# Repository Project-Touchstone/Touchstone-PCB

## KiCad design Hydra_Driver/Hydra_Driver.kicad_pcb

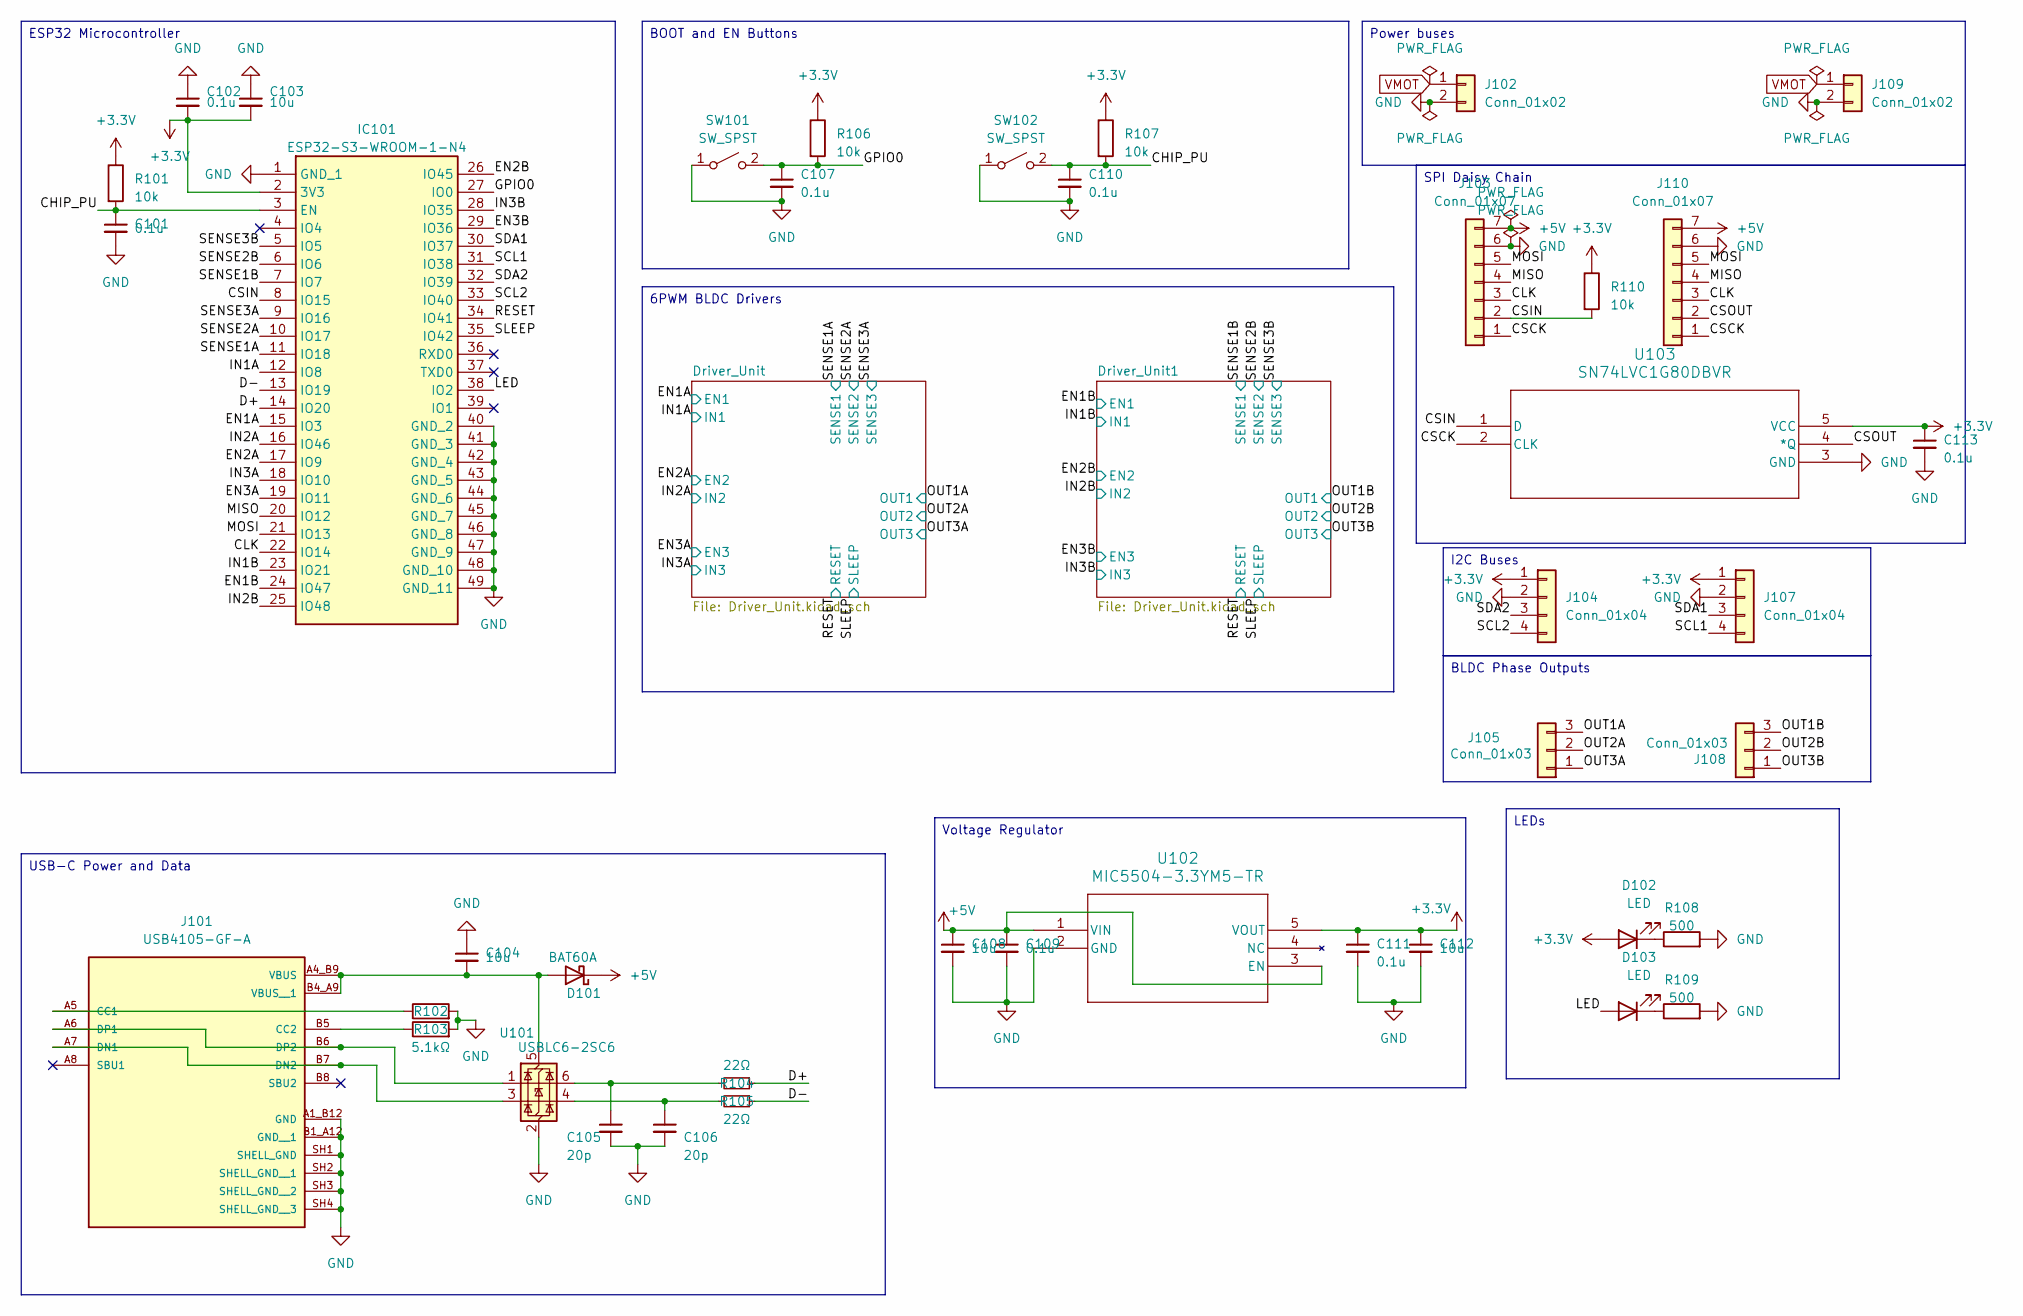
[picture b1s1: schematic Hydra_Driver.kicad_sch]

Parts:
C101, C102, C107, C109, C110, C111, C113: 0.1u; C_0402_1005Metric
C103, C104, C108, C112: 10u; C_0805_2012Metric
C105, C106: 20p; C_0402_1005Metric; LCSC C1648
D101: BAT60A; D_SOD-323; JLCPCB C124187
D102, D103: LED; LED_0603_1608Metric
IC101: ESP32-S3-WROOM-1-N4; ESP32S3WROOM1N4; Manufacturer_Part_Number ESP32-S3-WROOM-1-N4; Mouser Part Number 356-ESP32-S3WROOM1N4
J101: USB4105-GF-A; GCT_USB4105-GF-A; PARTREV B4
J102, J109: Conn_01x02; AMASS_XT30U-F_1x02_P5.0mm_Vertical
J103: Conn_01x07; PinSocket_1x07_P2.54mm_Horizontal
J104, J107: Conn_01x04; CONN_CCSH-W10R-04TR-BK-A_ADA
J105, J108: Conn_01x03; JST_XH_S3B-XH-A-1_1x03_P2.50mm_Horizontal
J110: Conn_01x07; PinHeader_1x07_P2.54mm_Horizontal
R101, R106, R107, R110: 10k; R_0402_1005Metric
R102, R103: 5.1kΩ; R_0402_1005Metric; JLCPCB C23186
R104, R105: 22Ω; R_0402_1005Metric; LCSC C23345
R108, R109: 500; R_0402_1005Metric
SW101, SW102: SW_SPST; SW_B3U-1000P
U101: USBLC6-2SC6; SOT-23-6; JLCPCB C2827654
U102: MIC5504-3.3YM5-TR; SOT-23-5_MC_MCH
U103: SN74LVC1G80DBVR; DBV5

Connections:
+3.3V: C102.2, C103.2, C111.1, C112.1, C113.1, D102.2 (A), IC101.2 (3V3), J104.1, J107.1, R101.1, R106.1, R107.1, R110.1, U102.5 (VOUT), U103.5 (VCC); also elsewhere on the board
+5V: C108.1, C109.1, D101.1 (K), J103.7, J110.7, U102.1 (VIN), U102.3 (EN)
/CHIP_PU: C101.1, C110.1, IC101.3 (EN), R101.2, R107.2, SW102.2 (B)
/CLK: IC101.22 (IO14), J103.3, J110.3
/CSCK: J103.1, J110.1, U103.2 (CLK)
/CSIN: IC101.8 (IO15), J103.2, R110.2, U103.1 (D)
/CSOUT: J110.2, U103.4 (*Q)
/D+: IC101.14 (IO20), R104.1
/D-: IC101.13 (IO19), R105.1
/EN1A: IC101.15 (IO3); also elsewhere on the board
/EN1B: IC101.24 (IO47); also elsewhere on the board
/EN2A: IC101.17 (IO9); also elsewhere on the board
/EN2B: IC101.26 (IO45); also elsewhere on the board
/EN3A: IC101.19 (IO11); also elsewhere on the board
/EN3B: IC101.29 (IO36); also elsewhere on the board
/GPIO0: C107.1, IC101.27 (IO0), R106.2, SW101.2 (B)
/IN1A: IC101.12 (IO8); also elsewhere on the board
/IN1B: IC101.23 (IO21); also elsewhere on the board
/IN2A: IC101.16 (IO46); also elsewhere on the board
/IN2B: IC101.25 (IO48); also elsewhere on the board
/IN3A: IC101.18 (IO10); also elsewhere on the board
/IN3B: IC101.28 (IO35); also elsewhere on the board
/LED: D103.2 (A), IC101.38 (IO2)
/MISO: IC101.20 (IO12), J103.4, J110.4
/MOSI: IC101.21 (IO13), J103.5, J110.5
/OUT1A: J105.3; also elsewhere on the board
/OUT1B: J108.3; also elsewhere on the board
/OUT2A: J105.2; also elsewhere on the board
/OUT2B: J108.2; also elsewhere on the board
/OUT3A: J105.1; also elsewhere on the board
/OUT3B: J108.1; also elsewhere on the board
/RESET: IC101.34 (IO41); also elsewhere on the board
/SCL1: IC101.31 (IO38), J107.4
/SCL2: IC101.33 (IO40), J104.4
/SDA1: IC101.30 (IO37), J107.3
/SDA2: IC101.32 (IO39), J104.3
/SENSE1A: IC101.11 (IO18); also elsewhere on the board
/SENSE1B: IC101.7 (IO7); also elsewhere on the board
/SENSE2A: IC101.10 (IO17); also elsewhere on the board
/SENSE2B: IC101.6 (IO6); also elsewhere on the board
/SENSE3A: IC101.9 (IO16); also elsewhere on the board
/SENSE3B: IC101.5 (IO5); also elsewhere on the board
/SLEEP: IC101.35 (IO42); also elsewhere on the board
GND: C101.2, C102.1, C103.1, C104.1, C105.2, C106.2, C107.2, C108.2, C109.2, C110.2, C111.2, C112.2, C113.2, IC101.1 (GND_1), IC101.40 (GND_2), IC101.41 (GND_3), IC101.42 (GND_4), IC101.43 (GND_5), IC101.44 (GND_6), IC101.45 (GND_7), IC101.46 (GND_8), IC101.47 (GND_9), IC101.48 (GND_10), IC101.49 (GND_11), J101.A1_B12 (GND), J101.B1_A12 (GND__1), J101.SH1 (SHELL_GND), J101.SH2 (SHELL_GND__1), J101.SH3 (SHELL_GND__2), J101.SH4 (SHELL_GND__3), J102.2, J103.6, J104.2, J107.2, J109.2, J110.6, R102.2, R103.2, R108.2, R109.2, SW101.1 (A), SW102.1 (A), U101.2 (GND), U102.2 (GND), U103.3 (GND); also elsewhere on the board
unnamed: C105.1, R104.2, U101.6 (I/O1)
unnamed: C106.1, R105.2, U101.4 (I/O2)
unnamed: C104.2, D101.2 (A), J101.A4_B9 (VBUS), J101.B4_A9 (VBUS__1), U101.5 (VBUS)
unnamed: D102.1 (K), R108.1
unnamed: D103.1 (K), R109.1
unnamed: J101.A5 (CC1), R102.1
unnamed: J101.B5 (CC2), R103.1
unnamed: J101.A7 (DN1), J101.B7 (DN2), U101.3 (I/O2)
unnamed: J101.A6 (DP1), J101.B6 (DP2), U101.1 (I/O1)
VMOT: J102.1, J109.1; also elsewhere on the board

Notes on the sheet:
BLDC Phase Outputs
I2C Buses
LEDs
ESP32 Microcontroller
BOOT and EN Buttons
Voltage Regulator
SPI Daisy Chain
Power buses
6PWM BLDC Drivers
USB-C Power and Data

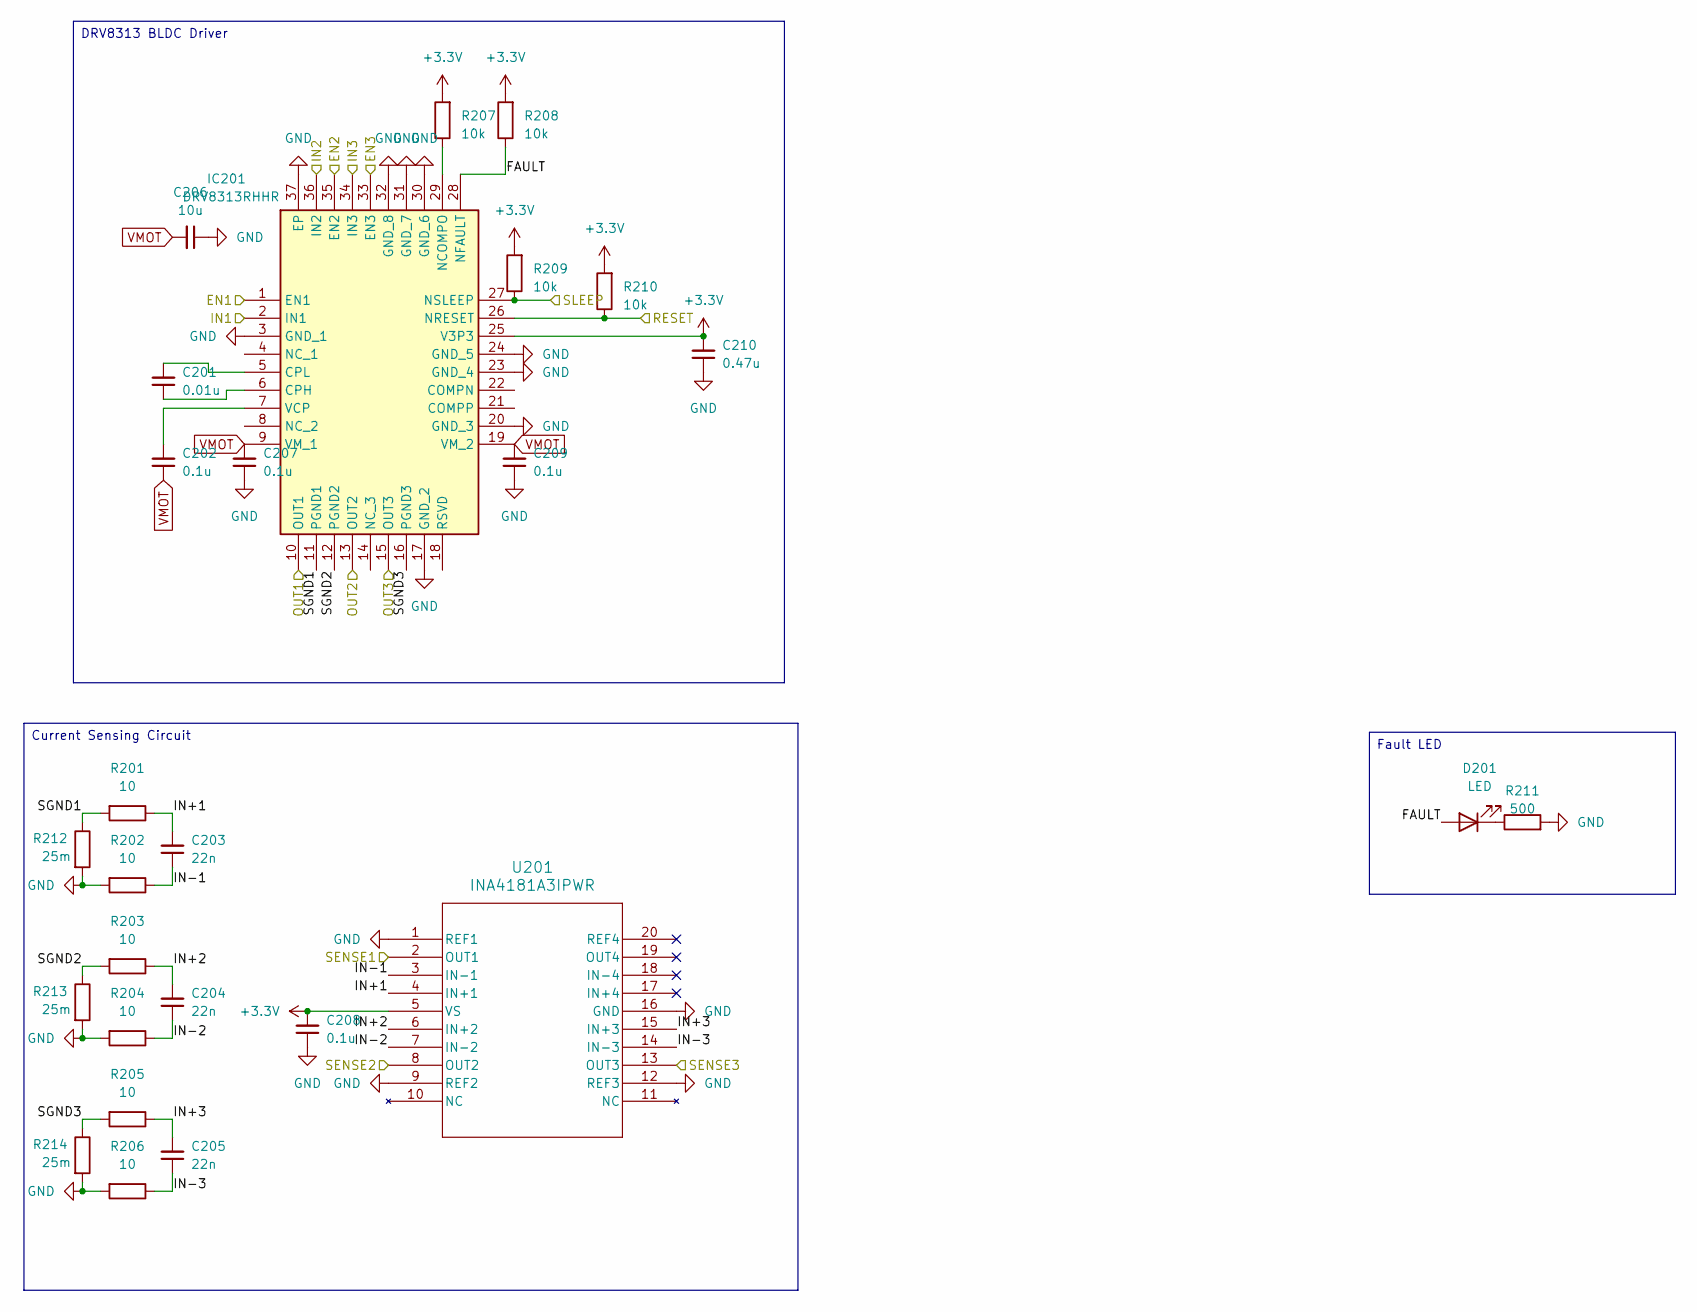
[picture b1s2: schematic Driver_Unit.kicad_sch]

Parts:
C201: 0.01u; C_0402_1005Metric
C202, C207, C208, C209: 0.1u; C_0402_1005Metric
C203, C204, C205: 22n; C_0402_1005Metric
C206: 10u; C_0805_2012Metric
C210: 0.47u; C_0402_1005Metric
D201: LED; LED_0603_1608Metric
IC201: DRV8313RHHR; QFN50P600X600X100-37N-D; Manufacturer_Part_Number DRV8313RHHR; Mouser Part Number 595-DRV8313RHHR
R201, R202, R203, R204, R205, R206: 10; R_0402_1005Metric
R207, R208, R209, R210: 10k; R_0402_1005Metric
R211: 500; R_0402_1005Metric
R212, R213, R214: 25m; R_1206_3216Metric
U201: INA4181A3IPWR; PW20_TEX

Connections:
+3.3V: C208.2, C210.2, IC201.25 (V3P3), R207.2, R208.2, R209.2, R210.2, U201.5 (VS); also elsewhere on the board
/Driver_Unit/FAULT: D201.2 (A), IC201.28 (NFAULT), R208.1
/Driver_Unit/IN+1: C203.2, R201.1, U201.4 (IN+1)
/Driver_Unit/IN+2: C204.2, R203.1, U201.6 (IN+2)
/Driver_Unit/IN+3: C205.2, R205.1, U201.15 (IN+3)
/Driver_Unit/IN-1: C203.1, R202.1, U201.3 (IN-1)
/Driver_Unit/IN-2: C204.1, R204.1, U201.7 (IN-2)
/Driver_Unit/IN-3: C205.1, R206.1, U201.14 (IN-3)
/Driver_Unit/SGND1: IC201.11 (PGND1), R201.2, R212.1
/Driver_Unit/SGND2: IC201.12 (PGND2), R203.2, R213.1
/Driver_Unit/SGND3: IC201.16 (PGND3), R205.2, R214.1
/EN1A: IC201.1 (EN1); also elsewhere on the board
/EN2A: IC201.35 (EN2); also elsewhere on the board
/EN3A: IC201.33 (EN3); also elsewhere on the board
/IN1A: IC201.2 (IN1); also elsewhere on the board
/IN2A: IC201.36 (IN2); also elsewhere on the board
/IN3A: IC201.34 (IN3); also elsewhere on the board
/OUT1A: IC201.10 (OUT1); also elsewhere on the board
/OUT2A: IC201.13 (OUT2); also elsewhere on the board
/OUT3A: IC201.15 (OUT3); also elsewhere on the board
/RESET: IC201.26 (NRESET), R210.1; also elsewhere on the board
/SENSE1A: U201.2 (OUT1); also elsewhere on the board
/SENSE2A: U201.8 (OUT2); also elsewhere on the board
/SENSE3A: U201.13 (OUT3); also elsewhere on the board
/SLEEP: IC201.27 (NSLEEP), R209.1; also elsewhere on the board
GND: C206.1, C207.1, C208.1, C209.1, C210.1, IC201.3 (GND_1), IC201.17 (GND_2), IC201.20 (GND_3), IC201.23 (GND_4), IC201.24 (GND_5), IC201.30 (GND_6), IC201.31 (GND_7), IC201.32 (GND_8), IC201.37 (EP), R202.2, R204.2, R206.2, R211.2, R212.2, R213.2, R214.2, U201.1 (REF1), U201.9 (REF2), U201.12 (REF3), U201.16 (GND); also elsewhere on the board
unnamed: D201.1 (K), R211.1
unnamed: C201.1, IC201.6 (CPH)
unnamed: C201.2, IC201.5 (CPL)
unnamed: IC201.29 (NCOMPO), R207.1
unnamed: C202.2, IC201.7 (VCP)
VMOT: C202.1, C206.2, C207.2, C209.2, IC201.9 (VM_1), IC201.19 (VM_2); also elsewhere on the board

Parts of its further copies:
C301: 0.01u; C_0402_1005Metric
C302, C307, C308, C309: 0.1u; C_0402_1005Metric
C306: 10u; C_0805_2012Metric
C310: 0.47u; C_0402_1005Metric
D301: LED; LED_0603_1608Metric
IC301: DRV8313RHHR; QFN50P600X600X100-37N-D; Manufacturer_Part_Number DRV8313RHHR; Mouser Part Number 595-DRV8313RHHR
R307, R308, R309, R310: 10k; R_0402_1005Metric
R311: 500; R_0402_1005Metric
R312, R313, R314: 25m; R_1206_3216Metric

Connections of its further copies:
+3.3V: C308.2, C310.2, IC301.25 (V3P3), R307.2, R308.2, R309.2, R310.2; also elsewhere on the board
/Driver_Unit1/FAULT: D301.2 (A), IC301.28 (NFAULT), R308.1
/Driver_Unit1/SGND1: IC301.11 (PGND1), R312.1; also elsewhere on the board
/Driver_Unit1/SGND2: IC301.12 (PGND2), R313.1; also elsewhere on the board
/Driver_Unit1/SGND3: IC301.16 (PGND3), R314.1; also elsewhere on the board
/EN1B: IC301.1 (EN1); also elsewhere on the board
/EN2B: IC301.35 (EN2); also elsewhere on the board
/EN3B: IC301.33 (EN3); also elsewhere on the board
/IN1B: IC301.2 (IN1); also elsewhere on the board
/IN2B: IC301.36 (IN2); also elsewhere on the board
/IN3B: IC301.34 (IN3); also elsewhere on the board
/OUT1B: IC301.10 (OUT1); also elsewhere on the board
/OUT2B: IC301.13 (OUT2); also elsewhere on the board
/OUT3B: IC301.15 (OUT3); also elsewhere on the board
/RESET: IC301.26 (NRESET), R310.1; also elsewhere on the board
/SLEEP: IC301.27 (NSLEEP), R309.1; also elsewhere on the board
GND: C306.1, C307.1, C308.1, C309.1, C310.1, IC301.3 (GND_1), IC301.17 (GND_2), IC301.20 (GND_3), IC301.23 (GND_4), IC301.24 (GND_5), IC301.30 (GND_6), IC301.31 (GND_7), IC301.32 (GND_8), IC301.37 (EP), R311.2, R312.2, R313.2, R314.2; also elsewhere on the board
unnamed: D301.1 (K), R311.1
unnamed: C301.1, IC301.6 (CPH)
unnamed: C301.2, IC301.5 (CPL)
unnamed: IC301.29 (NCOMPO), R307.1
unnamed: C302.2, IC301.7 (VCP)
VMOT: C302.1, C306.2, C307.2, C309.2, IC301.9 (VM_1), IC301.19 (VM_2); also elsewhere on the board

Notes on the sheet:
DRV8313 BLDC Driver
Fault LED
Current Sensing Circuit

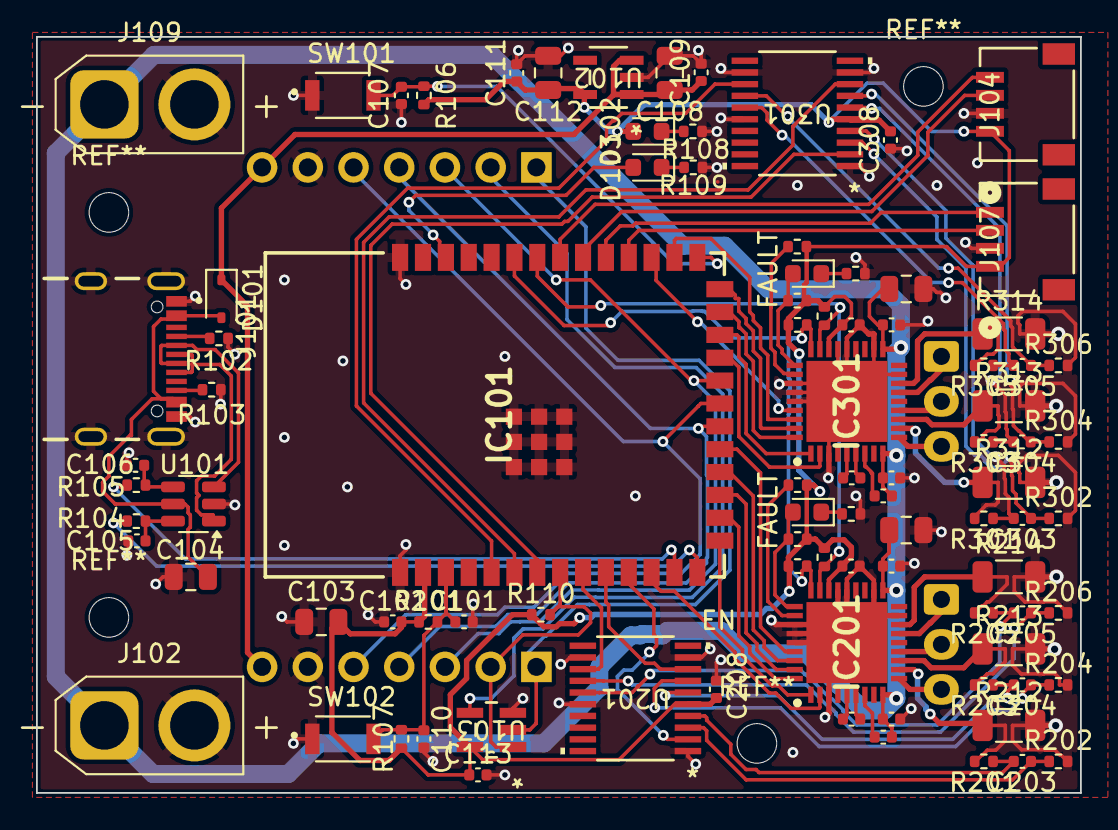
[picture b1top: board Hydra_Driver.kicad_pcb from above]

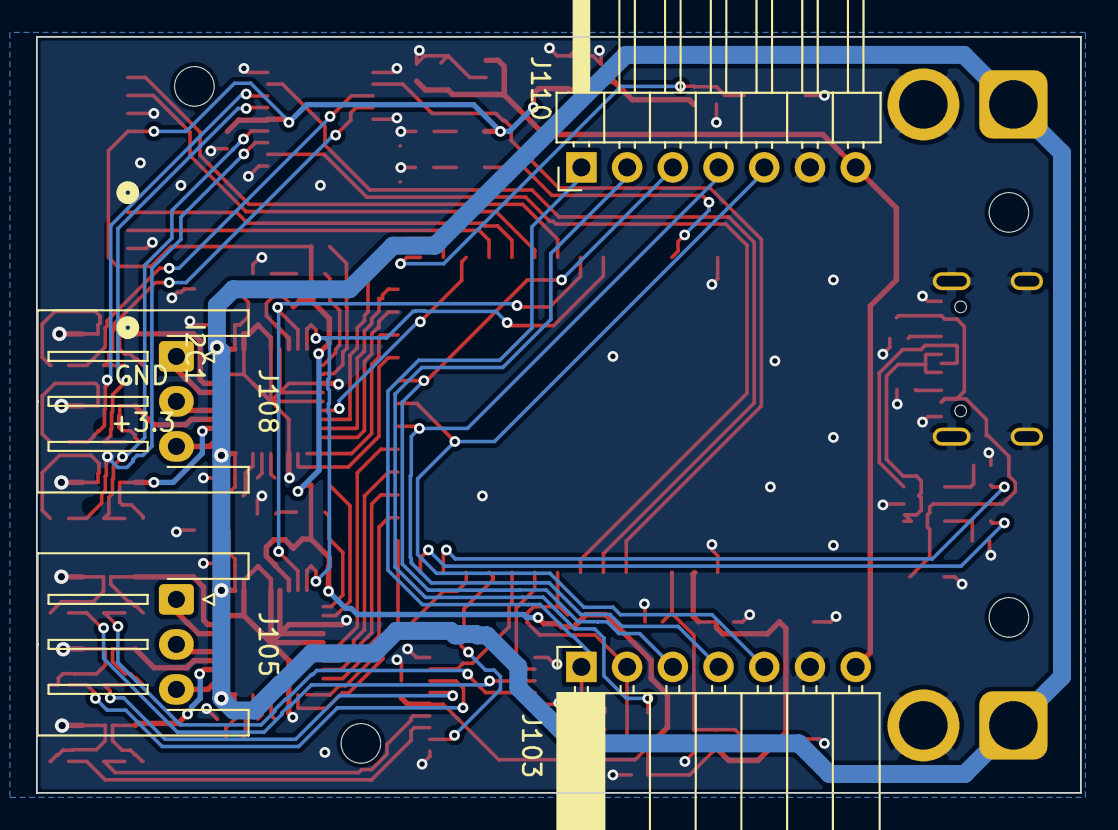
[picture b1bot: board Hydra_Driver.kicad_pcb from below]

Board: 2 copper layers, 58.0 x 42.0 mm, 95 parts (4 on the bottom side), 84 nets.

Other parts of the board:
C303, C304, C305: 1n; C_0402_1005Metric
R301, R302, R303, R304, R305, R306: 47; R_0402_1005Metric
U301: INA4181A2IPWR; PW20_TEX

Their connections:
+3.3V: U301.5 (VS); also elsewhere on the board
/Driver_Unit1/IN+1: C303.2, R301.1, U301.4 (IN+1)
/Driver_Unit1/IN+2: C304.2, R303.1, U301.6 (IN+2)
/Driver_Unit1/IN+3: C305.2, R305.1, U301.15 (IN+3)
/Driver_Unit1/IN-1: C303.1, R302.1, U301.3 (IN-1)
/Driver_Unit1/IN-2: C304.1, R304.1, U301.7 (IN-2)
/Driver_Unit1/IN-3: C305.1, R306.1, U301.14 (IN-3)
/Driver_Unit1/SGND1: R301.2; also elsewhere on the board
/Driver_Unit1/SGND2: R303.2; also elsewhere on the board
/Driver_Unit1/SGND3: R305.2; also elsewhere on the board
/SENSE1B: U301.2 (OUT1); also elsewhere on the board
/SENSE2B: U301.8 (OUT2); also elsewhere on the board
/SENSE3B: U301.13 (OUT3); also elsewhere on the board
GND: R302.2, R304.2, R306.2, U301.1 (REF1), U301.9 (REF2), U301.12 (REF3), U301.16 (GND); also elsewhere on the board

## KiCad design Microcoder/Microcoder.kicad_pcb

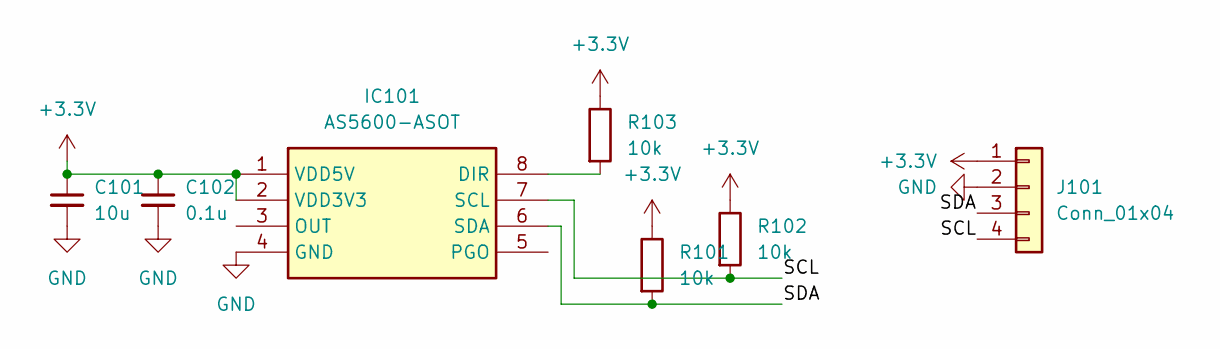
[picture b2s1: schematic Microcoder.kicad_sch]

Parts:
C101: 10u; C_0805_2012Metric
C102: 0.1u; C_0402_1005Metric
IC101: AS5600-ASOT; SOIC-8_3.9x4.9mm_P1.27mm; Manufacturer_Part_Number AS5600-ASOT; Mouser Part Number 985-AS5600-ASOT
J101: Conn_01x04; CONN_CCSH-W10R-04TR-BK-A_ADA
R101, R102, R103: 10k; R_0402_1005Metric

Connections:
+3.3V: C101.1, C102.1, IC101.1 (VDD5V), IC101.2 (VDD3V3), J101.1, R101.1, R102.1, R103.1
/SCL: IC101.7 (SCL), J101.4, R102.2
/SDA: IC101.6 (SDA), J101.3, R101.2
GND: C101.2, C102.2, IC101.4 (GND), J101.2
unnamed: IC101.8 (DIR), R103.2

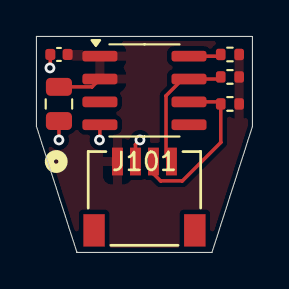
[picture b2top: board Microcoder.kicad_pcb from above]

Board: 2 copper layers, 12.0 x 12.0 mm, 7 parts (0 on the bottom side), 5 nets.

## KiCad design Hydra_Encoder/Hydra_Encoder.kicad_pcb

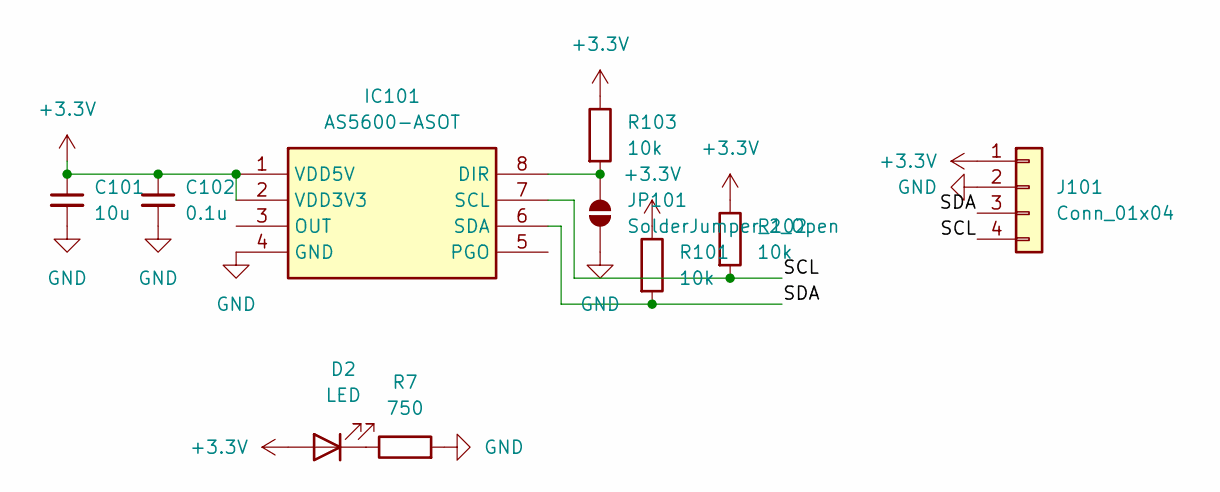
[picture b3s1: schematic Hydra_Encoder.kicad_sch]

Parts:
C101: 10u; C_0805_2012Metric
C102: 0.1u; C_0402_1005Metric
D2: LED; LED_0603_1608Metric
IC101: AS5600-ASOT; SOIC-8_3.9x4.9mm_P1.27mm; Manufacturer_Part_Number AS5600-ASOT; Mouser Part Number 985-AS5600-ASOT
J101: Conn_01x04; CONN_CCSH-W10R-04TR-BK-A_ADA
JP101: SolderJumper_2_Open; SolderJumper-2_P1.3mm_Open_RoundedPad1.0x1.5mm
R7: 750; R_0402_1005Metric
R101, R102, R103: 10k; R_0402_1005Metric

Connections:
+3.3V: C101.1, C102.1, D2.2 (A), IC101.1 (VDD5V), IC101.2 (VDD3V3), J101.1, R101.1, R102.1, R103.1
/SCL: IC101.7 (SCL), J101.4, R102.2
/SDA: IC101.6 (SDA), J101.3, R101.2
GND: C101.2, C102.2, IC101.4 (GND), J101.2, JP101.1 (A), R7.2
unnamed: D2.1 (K), R7.1
unnamed: IC101.8 (DIR), JP101.2 (B), R103.2

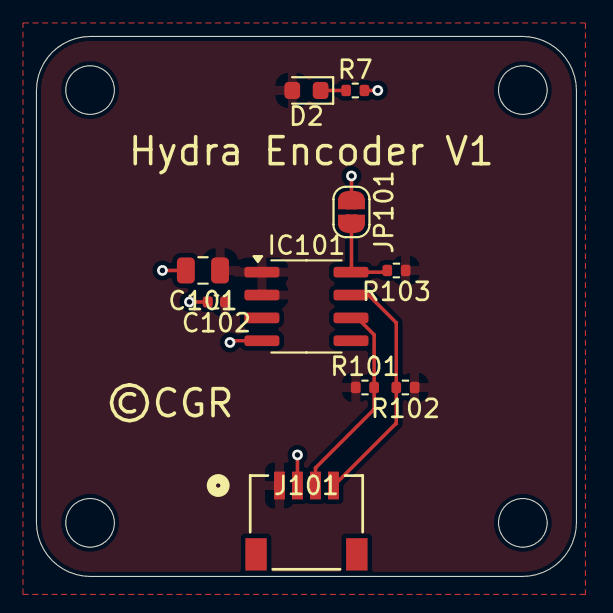
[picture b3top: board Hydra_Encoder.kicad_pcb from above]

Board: 2 copper layers, 30.0 x 30.0 mm, 10 parts (0 on the bottom side), 6 nets.

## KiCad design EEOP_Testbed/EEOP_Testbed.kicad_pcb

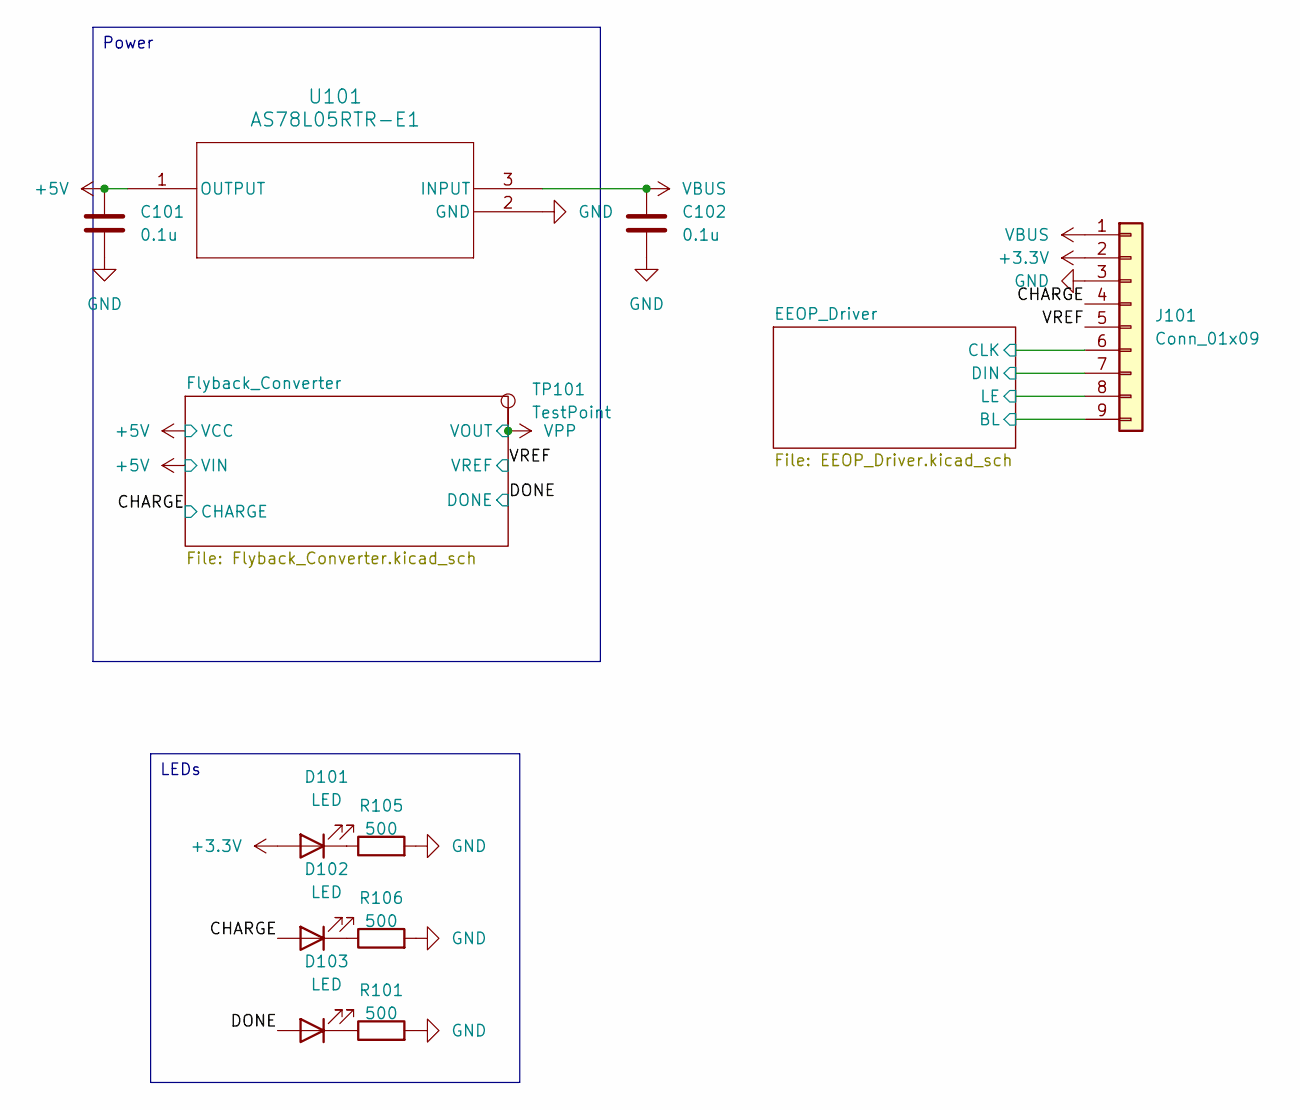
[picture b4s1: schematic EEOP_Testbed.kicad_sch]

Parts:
C101, C102: 0.1u; C_0402_1005Metric
D101, D102, D103: LED; LED_0603_1608Metric
J101: Conn_01x09; PinSocket_1x09_P2.54mm_Vertical
R101, R105, R106: 500; R_0402_1005Metric
TP101: TestPoint; TestPoint_Keystone_5019_Miniature
U101: AS78L05RTR-E1; SOT-89_3MC_MCH

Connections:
+3.3V: D101.2 (A), J101.2; also elsewhere on the board
+5V: C101.1, U101.1 (OUTPUT); also elsewhere on the board
/CHARGE: D102.2 (A), J101.4; also elsewhere on the board
/DONE: D103.2 (A); also elsewhere on the board
/EEOP_Driver/BL: J101.9; also elsewhere on the board
/EEOP_Driver/CLK: J101.6; also elsewhere on the board
/EEOP_Driver/DIN: J101.7; also elsewhere on the board
/EEOP_Driver/LE: J101.8; also elsewhere on the board
/VREF: J101.5; also elsewhere on the board
GND: C101.2, C102.2, J101.3, R101.2, R105.2, R106.2, U101.2 (GND); also elsewhere on the board
unnamed: D101.1 (K), R105.1
unnamed: D102.1 (K), R106.1
unnamed: D103.1 (K), R101.1
VBUS: C102.1, J101.1, U101.3 (INPUT); also elsewhere on the board
VPP: TP101.1; also elsewhere on the board

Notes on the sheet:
Power
LEDs

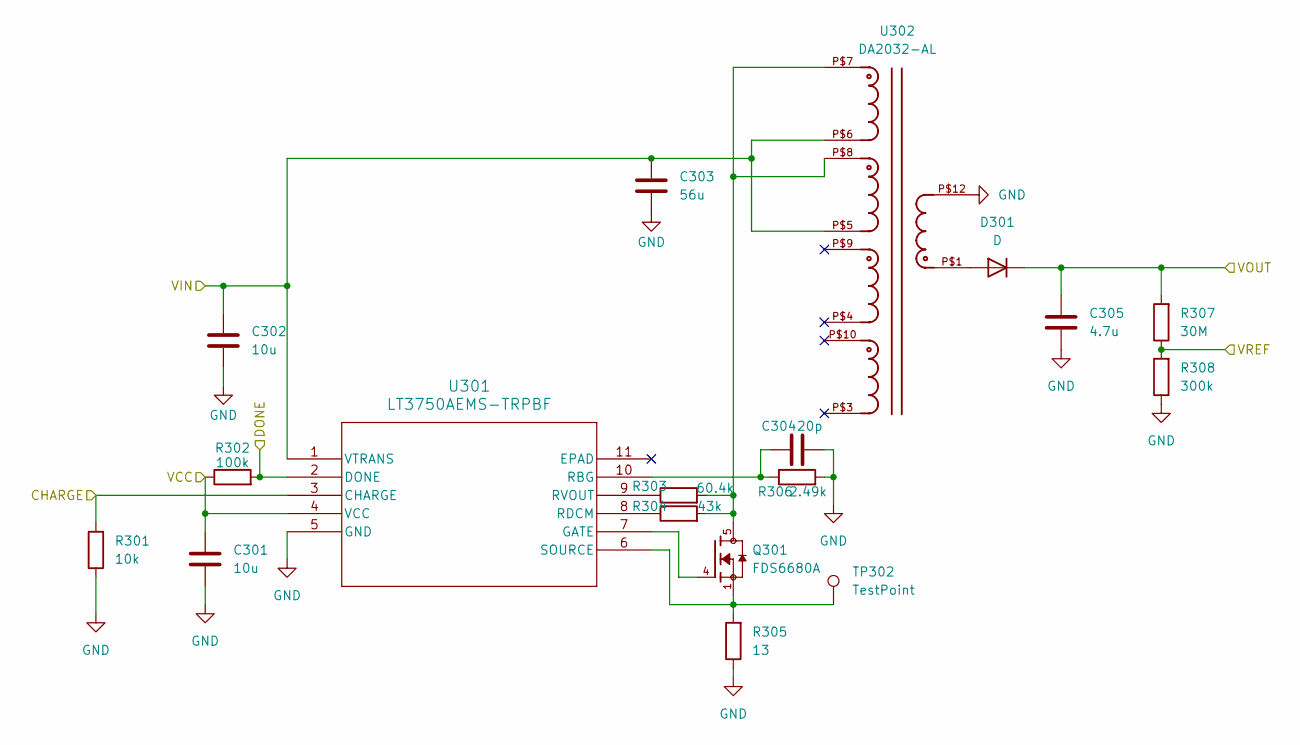
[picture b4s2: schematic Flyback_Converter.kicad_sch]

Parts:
C301, C302: 10u; C_0805_2012Metric
C303: 56u; C_Elec_6.3x5.8
C304: 20p; C_0402_1005Metric
C305: 4.7u; CP_Radial_D8.0mm_P3.50mm
D301: D; SMB_DIO
Q301: FDS6680A; SOIC127P600X175-8N; PARTREV 6; DigiKey_Part_Number FDS6680ACT-ND
R301: 10k; R_0402_1005Metric
R302: 100k; R_0402_1005Metric
R303: 60.4k; R_0402_1005Metric
R304: 43k; R_0402_1005Metric
R305: 13; R_0402_1005Metric
R306: 2.49k; R_0402_1005Metric
R307: 30M; R_0402_1005Metric
R308: 300k; R_0402_1005Metric
TP302: TestPoint; TestPoint_Keystone_5019_Miniature
U301: LT3750AEMS-TRPBF; MSOP-10-1EP_3x3mm_P0.5mm_EP1.68x1.88mm
U302: DA2032-AL

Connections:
+5V: C301.1, C302.1, C303.1, R302.1, U301.1 (VTRANS), U301.4 (VCC), U302.P$5, U302.P$6; also elsewhere on the board
/CHARGE: R301.2, U301.3 (CHARGE); also elsewhere on the board
/DONE: R302.2, U301.2 (DONE); also elsewhere on the board
/VREF: R307.1, R308.2; also elsewhere on the board
GND: C301.2, C302.2, C303.2, C304.1, C305.2, R301.1, R305.1, R306.2, R308.1, U301.5 (GND), U302.P$12; also elsewhere on the board
unnamed: D301.2 (A), U302.P$1
unnamed: Q301.5, Q301.6, Q301.7, Q301.8, R303.2, R304.2, U302.P$7, U302.P$8
unnamed: Q301.4, U301.7 (GATE)
unnamed: C304.2, R306.1, U301.10 (RBG)
unnamed: R304.1, U301.8 (RDCM)
unnamed: R303.1, U301.9 (RVOUT)
unnamed: Q301.1, Q301.2, Q301.3, R305.2, TP302.1, U301.6 (SOURCE)
VPP: C305.1, D301.1 (K), R307.2; also elsewhere on the board

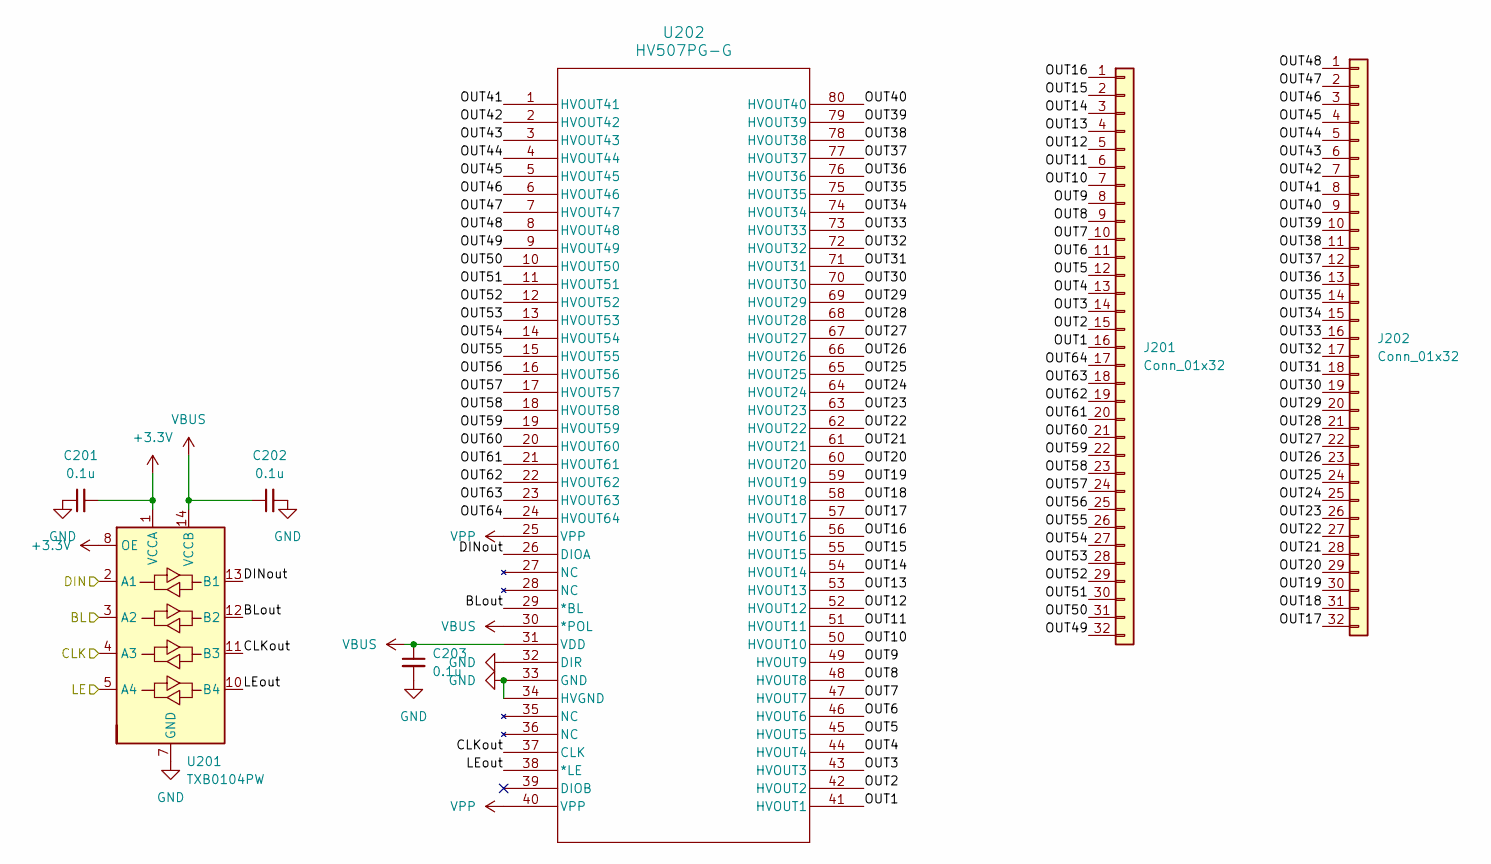
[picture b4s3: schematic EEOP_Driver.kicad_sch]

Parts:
C201, C202, C203: 0.1u; C_0402_1005Metric
J201, J202: Conn_01x32; HRS_FH34SRJ-32S-0.5SH_50_
U201: TXB0104PW; TSSOP-14_4.4x5mm_P0.65mm
U202: HV507PG-G; PQFP-80_14x20mm_P0.8mm

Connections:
+3.3V: C201.2, U201.1 (VCCA), U201.8 (OE); also elsewhere on the board
/EEOP_Driver/BL: U201.3 (A2); also elsewhere on the board
/EEOP_Driver/BLout: U201.12 (B2), U202.29 (*BL)
/EEOP_Driver/CLK: U201.4 (A3); also elsewhere on the board
/EEOP_Driver/CLKout: U201.11 (B3), U202.37 (CLK)
/EEOP_Driver/DIN: U201.2 (A1); also elsewhere on the board
/EEOP_Driver/DINout: U201.13 (B1), U202.26 (DIOA)
/EEOP_Driver/LE: U201.5 (A4); also elsewhere on the board
/EEOP_Driver/LEout: U201.10 (B4), U202.38 (*LE)
/EEOP_Driver/OUT1: J201.16, U202.41 (HVOUT1)
/EEOP_Driver/OUT2: J201.15, U202.42 (HVOUT2)
/EEOP_Driver/OUT3: J201.14, U202.43 (HVOUT3)
/EEOP_Driver/OUT4: J201.13, U202.44 (HVOUT4)
/EEOP_Driver/OUT5: J201.12, U202.45 (HVOUT5)
/EEOP_Driver/OUT6: J201.11, U202.46 (HVOUT6)
/EEOP_Driver/OUT7: J201.10, U202.47 (HVOUT7)
/EEOP_Driver/OUT8: J201.9, U202.48 (HVOUT8)
/EEOP_Driver/OUT9: J201.8, U202.49 (HVOUT9)
/EEOP_Driver/OUT10: J201.7, U202.50 (HVOUT10)
/EEOP_Driver/OUT11: J201.6, U202.51 (HVOUT11)
/EEOP_Driver/OUT12: J201.5, U202.52 (HVOUT12)
/EEOP_Driver/OUT13: J201.4, U202.53 (HVOUT13)
/EEOP_Driver/OUT14: J201.3, U202.54 (HVOUT14)
/EEOP_Driver/OUT15: J201.2, U202.55 (HVOUT15)
/EEOP_Driver/OUT16: J201.1, U202.56 (HVOUT16)
/EEOP_Driver/OUT17: J202.32, U202.57 (HVOUT17)
/EEOP_Driver/OUT18: J202.31, U202.58 (HVOUT18)
/EEOP_Driver/OUT19: J202.30, U202.59 (HVOUT19)
/EEOP_Driver/OUT20: J202.29, U202.60 (HVOUT20)
/EEOP_Driver/OUT21: J202.28, U202.61 (HVOUT21)
/EEOP_Driver/OUT22: J202.27, U202.62 (HVOUT22)
/EEOP_Driver/OUT23: J202.26, U202.63 (HVOUT23)
/EEOP_Driver/OUT24: J202.25, U202.64 (HVOUT24)
/EEOP_Driver/OUT25: J202.24, U202.65 (HVOUT25)
/EEOP_Driver/OUT26: J202.23, U202.66 (HVOUT26)
/EEOP_Driver/OUT27: J202.22, U202.67 (HVOUT27)
/EEOP_Driver/OUT28: J202.21, U202.68 (HVOUT28)
/EEOP_Driver/OUT29: J202.20, U202.69 (HVOUT29)
/EEOP_Driver/OUT30: J202.19, U202.70 (HVOUT30)
/EEOP_Driver/OUT31: J202.18, U202.71 (HVOUT31)
/EEOP_Driver/OUT32: J202.17, U202.72 (HVOUT32)
/EEOP_Driver/OUT33: J202.16, U202.73 (HVOUT33)
/EEOP_Driver/OUT34: J202.15, U202.74 (HVOUT34)
/EEOP_Driver/OUT35: J202.14, U202.75 (HVOUT35)
/EEOP_Driver/OUT36: J202.13, U202.76 (HVOUT36)
/EEOP_Driver/OUT37: J202.12, U202.77 (HVOUT37)
/EEOP_Driver/OUT38: J202.11, U202.78 (HVOUT38)
/EEOP_Driver/OUT39: J202.10, U202.79 (HVOUT39)
/EEOP_Driver/OUT40: J202.9, U202.80 (HVOUT40)
/EEOP_Driver/OUT41: J202.8, U202.1 (HVOUT41)
/EEOP_Driver/OUT42: J202.7, U202.2 (HVOUT42)
/EEOP_Driver/OUT43: J202.6, U202.3 (HVOUT43)
/EEOP_Driver/OUT44: J202.5, U202.4 (HVOUT44)
/EEOP_Driver/OUT45: J202.4, U202.5 (HVOUT45)
/EEOP_Driver/OUT46: J202.3, U202.6 (HVOUT46)
/EEOP_Driver/OUT47: J202.2, U202.7 (HVOUT47)
/EEOP_Driver/OUT48: J202.1, U202.8 (HVOUT48)
/EEOP_Driver/OUT49: J201.32, U202.9 (HVOUT49)
/EEOP_Driver/OUT50: J201.31, U202.10 (HVOUT50)
/EEOP_Driver/OUT51: J201.30, U202.11 (HVOUT51)
/EEOP_Driver/OUT52: J201.29, U202.12 (HVOUT52)
/EEOP_Driver/OUT53: J201.28, U202.13 (HVOUT53)
/EEOP_Driver/OUT54: J201.27, U202.14 (HVOUT54)
/EEOP_Driver/OUT55: J201.26, U202.15 (HVOUT55)
/EEOP_Driver/OUT56: J201.25, U202.16 (HVOUT56)
/EEOP_Driver/OUT57: J201.24, U202.17 (HVOUT57)
/EEOP_Driver/OUT58: J201.23, U202.18 (HVOUT58)
/EEOP_Driver/OUT59: J201.22, U202.19 (HVOUT59)
/EEOP_Driver/OUT60: J201.21, U202.20 (HVOUT60)
/EEOP_Driver/OUT61: J201.20, U202.21 (HVOUT61)
/EEOP_Driver/OUT62: J201.19, U202.22 (HVOUT62)
/EEOP_Driver/OUT63: J201.18, U202.23 (HVOUT63)
/EEOP_Driver/OUT64: J201.17, U202.24 (HVOUT64)
GND: C201.1, C202.2, C203.2, U201.7 (GND), U202.32 (DIR), U202.33 (GND), U202.34 (HVGND); also elsewhere on the board
VBUS: C202.1, C203.1, U201.14 (VCCB), U202.30 (*POL), U202.31 (VDD); also elsewhere on the board
VPP: U202.25 (VPP), U202.40 (VPP); also elsewhere on the board

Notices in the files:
Hydra_Encoder/Hydra_Encoder.kicad_pcb:
©CGR
